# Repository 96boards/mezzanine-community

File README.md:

# 96boards Community Mezzanine Initiative

## About this Project

This is a community led, organized and maintained initiative. This repository is for designing mezzanine addon boards based on the 96Boards family of [96boards specifications](https://www.96boards.org/specifications/).

## Contributing and Reporting Issues

Community contributions are always Welcome! Before contributing to a project, first get the approval from maintainer by raising a GitHub issue using the following guidelines.

Take a look at our [CONTRIBUTE.md](CONTRIBUTE.md) page for more info.

## Roadmap and Wishlist

- Quantized community 96Boards Mezzanine input
- More boards!

## Meetings and notes

An informal steering committee of community members will allocate resources to a variety or projects, all with a grand scope of meeting the needs of the greater 96Boards community.

-  Bi Weekly voice/video conference meetings are open to the public on the 96Boards Discord Server. Join every Every 2 weeks on Monday at 16:00 UTC to take part in the discussion.
   - https://discord.gg/TC3pv8XcN8
- [View notes](https://github.com/96boards/mezzanine-community/issues?q=is%3Aissue+is%3Aopen+label%3AMeeting) from previous meetings

## Acknowledgement

- T.Krug @sad_electronics - Lead Maintainer
- Michael Welling, mwelling@ieee.org - Maintainer
- Robert Wolff, robert.wolff@linaro.org - Community
- Rafael Christ, rafaelchrist@gmail.com - Altium / Eagle Reviewer
- Gustavo Retuci Pinheiro, gustavo_r_p@hotmail.com - Altium / Eagle Reviewer
- Sahaj Sarup, sahajsarup@gmail.com - Reviewer
- Grant Likely, grant.likely@secretlab.ca - KiCad contributor
- Sophie Haynes - KiCad contributor

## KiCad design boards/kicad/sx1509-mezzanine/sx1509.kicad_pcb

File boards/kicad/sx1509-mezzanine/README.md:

# 96boards Mezzanine Project Template

This template provides you with all the base files required for 
a 96Boards mezzanine pcb project.

#### Template Folder Contents:

- COPYING (license)
- meta
- 96boards.pretty (folder containing footprints) °
- mezza-cache.lib ° (system file, ignore)
- mezza.pro °
- mezza.sch °
- mezza.kicad_pcb °
- fp-lib-table °

*Files marked with ° are the KiCad project files*

## To-Do's

Coming soon...

## What is this template for?

This is a template for anyone who wants to develop a Consumer Edition 96Boards
Mezzanine board - [List of Consumer Edition Boards](https://www.96boards.org/products/ce/)

This schematic only contains the necessary connectors needed
for a mezzanine board. By default it is set up for SMD connectors, but
can easily be changed to through-hole.

The <em>PCB</em> includes the connectors and mounting holes. The holes
and connectors have been positioned so that the boards are aligned when
mounted. The <em>edge cuts</em> also aligns with the base board. All the
mezzanine board low-speed expansion connector <em>IO</em> is connected
to the header pins. High-speed expansion IO has not yet been added.

## How to use this project

This project has been formatted to work with KiCad's "New Project from
Template" tool. You should clone this project into your KiCad templates
directory. For example, on OSX the system template directory is
<em>/Library/Application Support/kicad/template/</em>. A Linux user's
template directory is <em>$HOME/kicad/template/</em>

Once cloned, you can use the new template by navigating to
File > New Project > New Project From Template. After selecting your
save location, click on <em>System Templates</em> or <em>User
Templates</em> (depending on which file path you previously selected to
clone the project to). Upon validation of the file path, the 96Boards
mezzanine template should appear under the 96Boards logo. Select the
template and you'll be good to go.

## Changing to Through Hole Connector

By default, this project loads with the connectors set up as SMD. If you
would prefer to use a through hole instead, follow the instructions on
the schematic to delete a connector and change the footprint on the
other. To change the footprint, right click and select <em>Edit
Component</em>. In the dialog box, click on the footprint section, then
on the right there should now be a button called <em>Assign
Footprint</em>. Click the button, and choose the different footprint
file. Create a new netlist file, open up the PCB editor, and <em>Load
Netlist</em>, ensuring that <em>Exchange Footprint</em> is set to
CHANGE, and <em>Extra Footprints</em> is set to DELETE. Click <em>Read
Current Netlist</em> to load the new connector. Now you should have only
one connector on the board, and when you view in 3D view, there will be
a through hole connector.

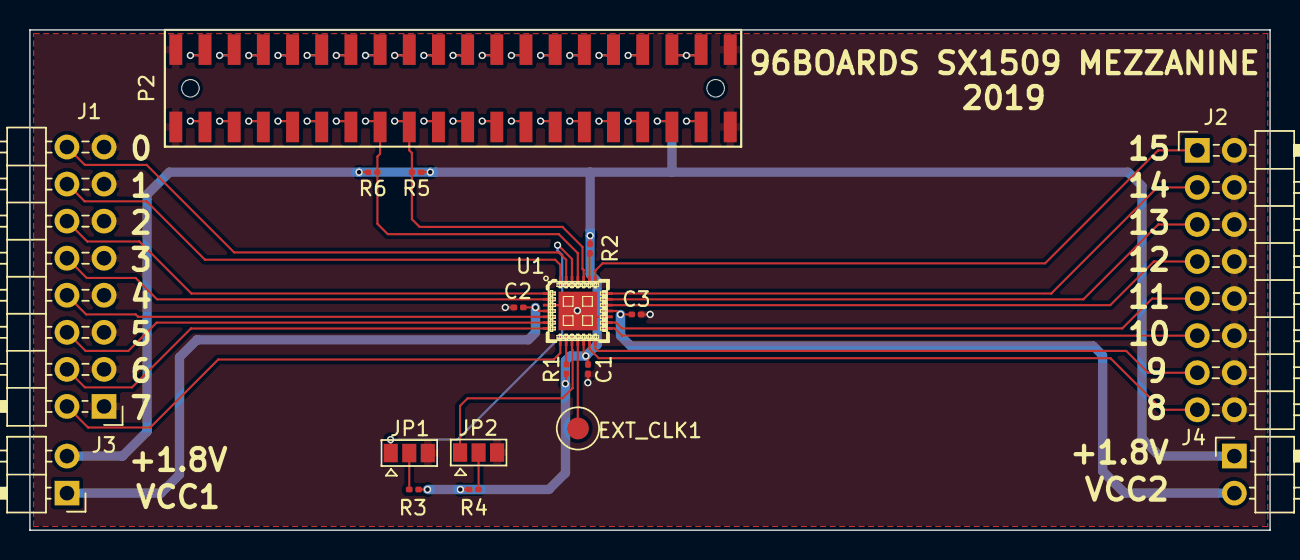
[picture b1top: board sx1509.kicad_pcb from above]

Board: 2 copper layers, 85.0 x 34.3 mm, 19 parts (1 on the bottom side), 61 nets.

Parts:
C1, C2, C3: 0.1uF; C_0201_0603Metric
EXT_CLK1: TestPoint; TestPoint_Pad_D2.5mm
J1, J2: Conn_02x08_Odd_Even; PinHeader_2x08_P2.54mm_Horizontal
J3, J4: Conn_01x02_Male; PinHeader_1x02_P2.54mm_Horizontal
JP1, JP2: Jumper_NC_Dual; SolderJumper_01x03
P1: CONN_02X20; Pin_Header_SMD_2x20_Pitch2mm
P2: CONN_02X20; Socket_Strip_SMD_2x20_Pitch2mm
R1, R2, R3, R4, R5, R6: 10K; R_0201_0603Metric
U1: SX1509; QFN-28

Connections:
+1V8: C1.1, J3.2, J4.1, P1.35, P2.35, R1.2, R2.2, R3.2, R4.1, R5.1, R6.1, U1.12
+5V: P1.37, P2.37
ADDR0: JP1.1, U1.26
ADDR1: JP2.1, U1.10
GND: C1.2, C2.2, C3.2, J1.1, J1.3, J1.5, J1.7, J1.9, J1.11, J1.13, J1.15, J2.2, J2.4, J2.6, J2.8, J2.10, J2.12, J2.14, J2.16, JP1.3, JP2.3, P1.1, P1.2, P1.39, P1.40, P2.1, P2.2, P2.39, P2.40, U1.3, U1.17, U1.29
GPIO_A: P1.23, P2.23
GPIO_B: P1.24, P2.24
GPIO_C: P1.25, P2.25
GPIO_D: P1.26, P2.26
GPIO_E: P1.27, P2.27
GPIO_F: P1.28, P2.28
GPIO_G: P1.29, P2.29
GPIO_H: P1.30, P2.30
GPIO_I: P1.31, P2.31
GPIO_J: P1.32, P2.32
GPIO_K: P1.33, P2.33
GPIO_L: P1.34, P2.34
I2C0_SCL: P1.15, P2.15, R6.2, U1.25
I2C0_SDA: P1.17, P2.17, R5.2, U1.24
I2C1_SCL: P1.19, P2.19
I2C1_SDA: P1.21, P2.21
IO_0: J1.16, U1.27
IO_1: J1.14, U1.28
IO_2: J1.12, U1.1
IO_3: J1.10, U1.2
IO_4: J1.8, U1.5
IO_5: J1.6, U1.6
IO_6: J1.4, U1.7
IO_7: J1.2, U1.8
IO_8: J2.15, U1.13
IO_9: J2.13, U1.14
IO_10: J2.11, U1.15
IO_11: J2.9, U1.16
IO_12: J2.7, U1.19
IO_13: J2.5, U1.20
IO_14: J2.3, U1.21
IO_15: J2.1, U1.22
unnamed: EXT_CLK1.1, U1.11
unnamed: JP1.2, R3.1
unnamed: JP2.2, R4.2
unnamed: R1.1, U1.9
unnamed: R2.1, U1.23
PCM_CLK: P1.18, P2.18
PCM_DI: P1.22, P2.22
PCM_DO: P1.20, P2.20
PCM_FS: P1.16, P2.16
PWR_BTN_N: P1.4, P2.4
RST_BTN_N: P1.6, P2.6
SPIO_CS: P1.12, P2.12
SPIO_DIN: P1.10, P2.10
SPIO_DOUT: P1.14, P2.14
SPIO_SCL: P1.8, P2.8
SYS_DCIN: P1.36, P1.38, P2.36, P2.38
UART0_CTS: P1.3, P2.3
UART0_RTS: P1.9, P2.9
UART0_RX: P1.7, P2.7
UART0_TX: P1.5, P2.5
UART1_RX: P1.13, P2.13
UART1_TX: P1.11, P2.11
VCC1: C2.1, J3.1, U1.4
VCC2: C3.1, J4.2, U1.18

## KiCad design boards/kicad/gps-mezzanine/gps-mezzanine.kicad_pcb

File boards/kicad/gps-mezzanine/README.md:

# 96boards GPS Mezzanine

This project contains the design files for a GPS mezzanine for the 96boards CE specification.

Copyright (c) 2017-2018, Michael Welling

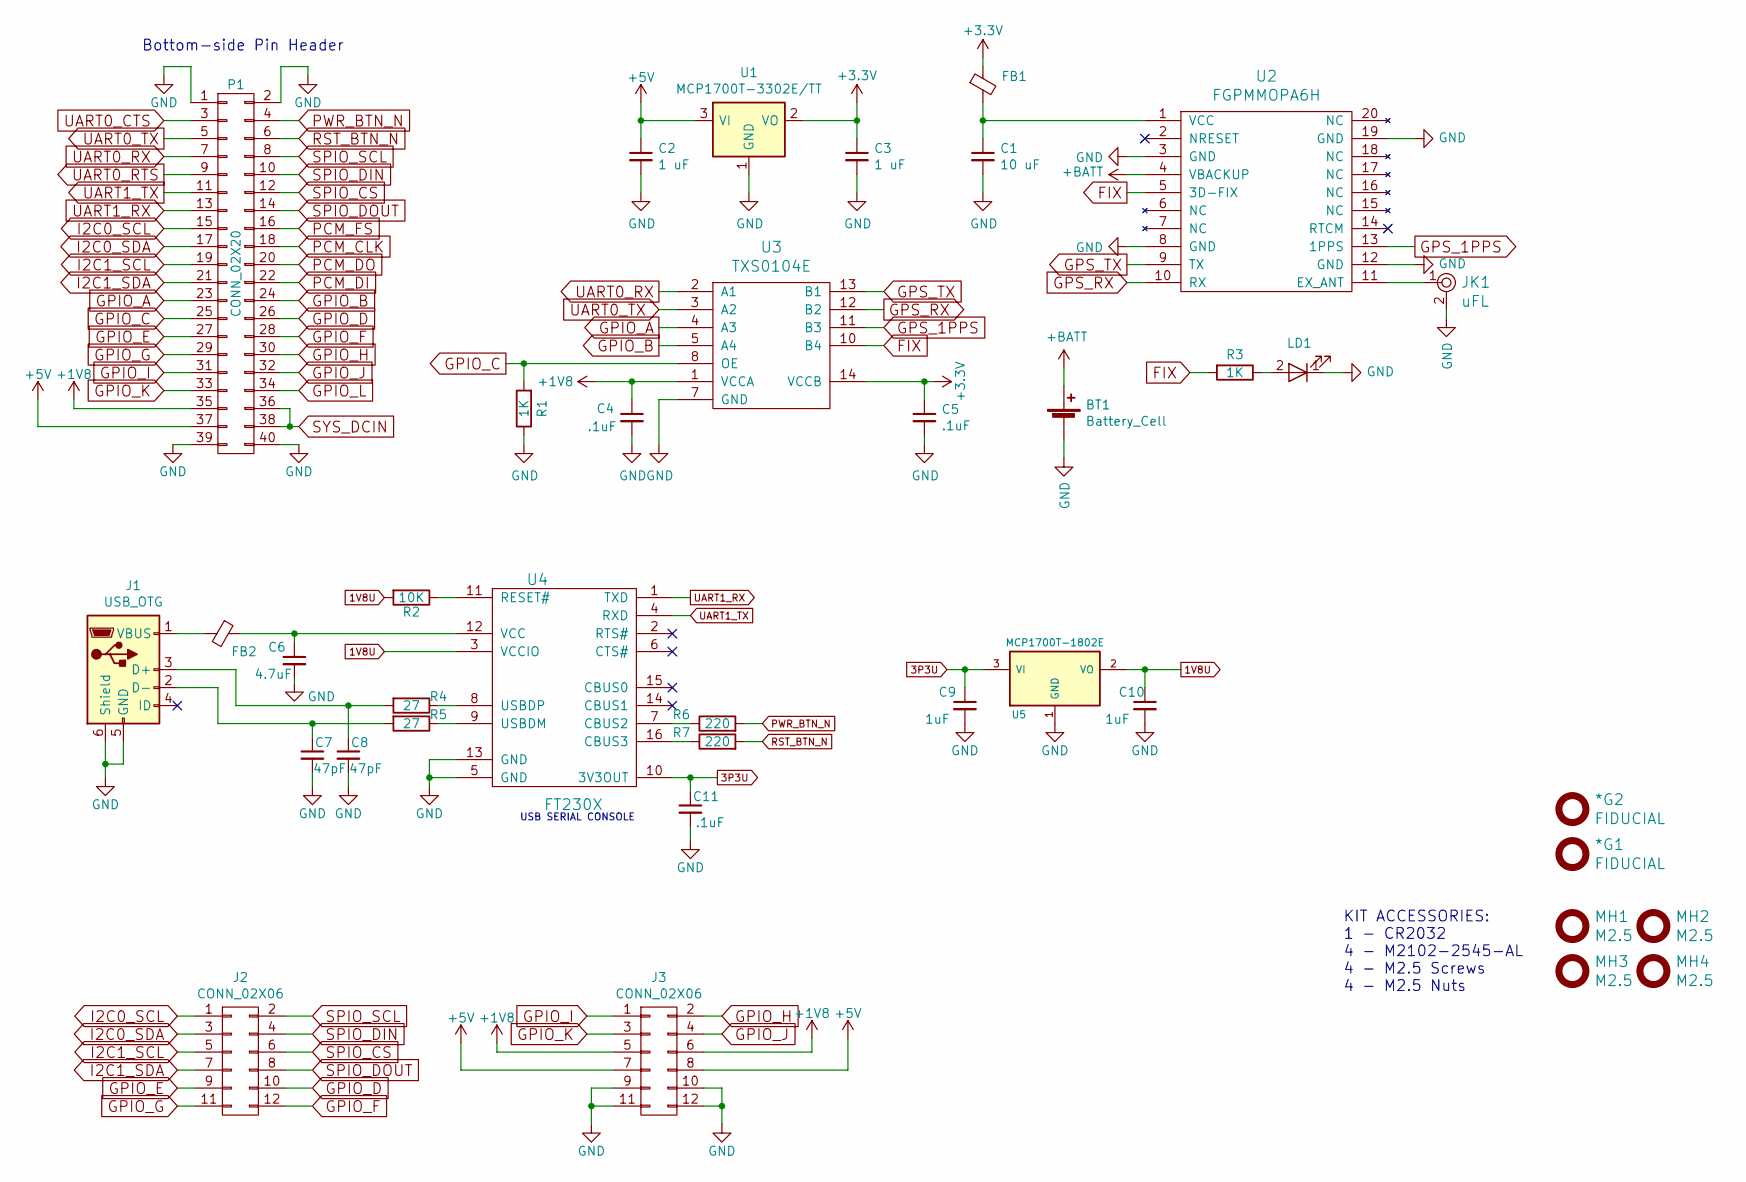
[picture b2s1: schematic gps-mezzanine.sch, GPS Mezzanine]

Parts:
*G1, *G2: FIDUCIAL; Fiducial_1mm_Dia_2.00mm_Outer_CopperTop
BT1: Battery_Cell; BAT-HLD-001; Mfg Part Number BAT-HLD-001-TR
C1: 10 uF; C_0603
C2, C3: 1 uF; C_0603
C4, C5, C11: .1uF; C_0603
C6: 4.7uF; C_0603
C7, C8: 47pF; C_0603
C9, C10: 1uF; C_0603
FB1, FB2: ILBB0805ER102V; R_0805_HandSoldering; Mfg Part Number ILBB0805ER102V
J1: USB_OTG; 10118192-0001LF(MICRO-USB-B-AMPHENOL-FCI); Mfg Part Number 10118192-0001LF
J2, J3: CONN_02X06; Pin_Header_Straight_2x06
JK1: uFL; U.FL-R-SMT-1; Mfg Part Number U.FL-R-SMT-1
LD1: LED; LED-0603
MH1, MH2, MH3, MH4: M2.5; MountingHole_2-5mm
P1: CONN_02X20; Pin_Header_SMD_2x20_Pitch2mm; Mfg Part Number 57202-G52-20LF
R1, R3: 1K; R_0603
R2: 10K; R_0603
R4, R5: 27; R_0603
R6, R7: 220; R_0603
U1: MCP1700T-3302E/TT; SOT-23; Mfg Part Number MCP1700T-3302E/TT
U2: FGPMMOPA6H; Mfg Part Number FGPMMOPA6H
U3: TXS0104E; TSSOP-14_4.3x5.1mm_Pitch0.65mm; Mfg Part Number TXS0104EPWR
U4: FT230X; SSOP-16_3.9x4.9mm_Pitch0.635mm; Mfg Part Number FT230XS-R
U5: MCP1700T-1802E; SOT-23; Mfg Part Number MCP1700T-1802E/TT

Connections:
1V8U: C10.1, R2.2, U4.3 (VCCIO), U5.2 (VO)
3P3U: C9.1, C11.1, U4.10 (3V3OUT), U5.3 (VI)
+1V8: C4.1, J3.5, J3.6, P1.35, U3.1 (VCCA)
+3V3: C3.1, C5.1, FB1.1, U1.2 (VO), U3.14 (VCCB)
+5V: C2.1, J3.7, J3.8, P1.37, U1.3 (VI)
+BATT: BT1.1 (+), U2.4 (VBACKUP)
FIX: R3.2, U2.5 (3D-FIX), U3.10 (B4)
GND: BT1.2 (-), C1.2, C2.2, C3.2, C4.2, C5.2, C6.2, C7.2, C8.2, C9.2, C10.2, C11.2, J1.5 (GND), J1.6 (Shield), J3.9, J3.10, J3.11, J3.12, JK1.2, LD1.1 (K), P1.1, P1.2, P1.39, P1.40, R1.1, U1.1 (GND), U2.3 (GND), U2.8 (GND), U2.12 (GND), U2.19 (GND), U3.7 (GND), U4.5 (GND), U4.13 (GND), U5.1 (GND)
GPIO_A: P1.23, U3.4 (A3)
GPIO_B: P1.24, U3.5 (A4)
GPIO_C: P1.25, R1.2, U3.8 (OE)
GPIO_D: J2.10, P1.26
GPIO_E: J2.9, P1.27
GPIO_F: J2.12, P1.28
GPIO_G: J2.11, P1.29
GPIO_H: J3.2, P1.30
GPIO_I: J3.1, P1.31
GPIO_J: J3.4, P1.32
GPIO_K: J3.3, P1.33
GPIO_L: P1.34
GPS_1PPS: U2.13 (1PPS), U3.11 (B3)
GPS_RX: U2.10 (RX), U3.12 (B2)
GPS_TX: U2.9 (TX), U3.13 (B1)
I2C0_SCL: J2.1, P1.15
I2C0_SDA: J2.3, P1.17
I2C1_SCL: J2.5, P1.19
I2C1_SDA: J2.7, P1.21
unnamed: C1.1, FB1.2, U2.1 (VCC)
unnamed: C6.1, FB2.1, U4.12 (VCC)
unnamed: C7.1, J1.2 (D-), R5.2
unnamed: C8.1, J1.3 (D+), R4.2
unnamed: FB2.2, J1.1 (VBUS)
unnamed: JK1.1, U2.11 (EX_ANT)
unnamed: LD1.2 (A), R3.1
unnamed: R2.1, U4.11 (RESET#)
unnamed: R4.1, U4.8 (USBDP)
unnamed: R5.1, U4.9 (USBDM)
unnamed: R6.1, U4.7 (CBUS2)
unnamed: R7.1, U4.16 (CBUS3)
PCM_CLK: P1.18
PCM_DI: P1.22
PCM_DO: P1.20
PCM_FS: P1.16
PWR_BTN_N: P1.4, R6.2
RST_BTN_N: P1.6, R7.2
SPIO_CS: J2.6, P1.12
SPIO_DIN: J2.4, P1.10
SPIO_DOUT: J2.8, P1.14
SPIO_SCL: J2.2, P1.8
SYS_DCIN: P1.36, P1.38
UART0_CTS: P1.3
UART0_RTS: P1.9
UART0_RX: P1.7, U3.2 (A1)
UART0_TX: P1.5, U3.3 (A2)
UART1_RX: P1.13, U4.1 (TXD)
UART1_TX: P1.11, U4.4 (RXD)

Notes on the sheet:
Bottom-side Pin Header
KIT ACCESSORIES: 1 - CR2032 4 - M2102-2545-AL 4 - M2.5 Screws 4 - M2.5 Nuts
USB SERIAL CONSOLE

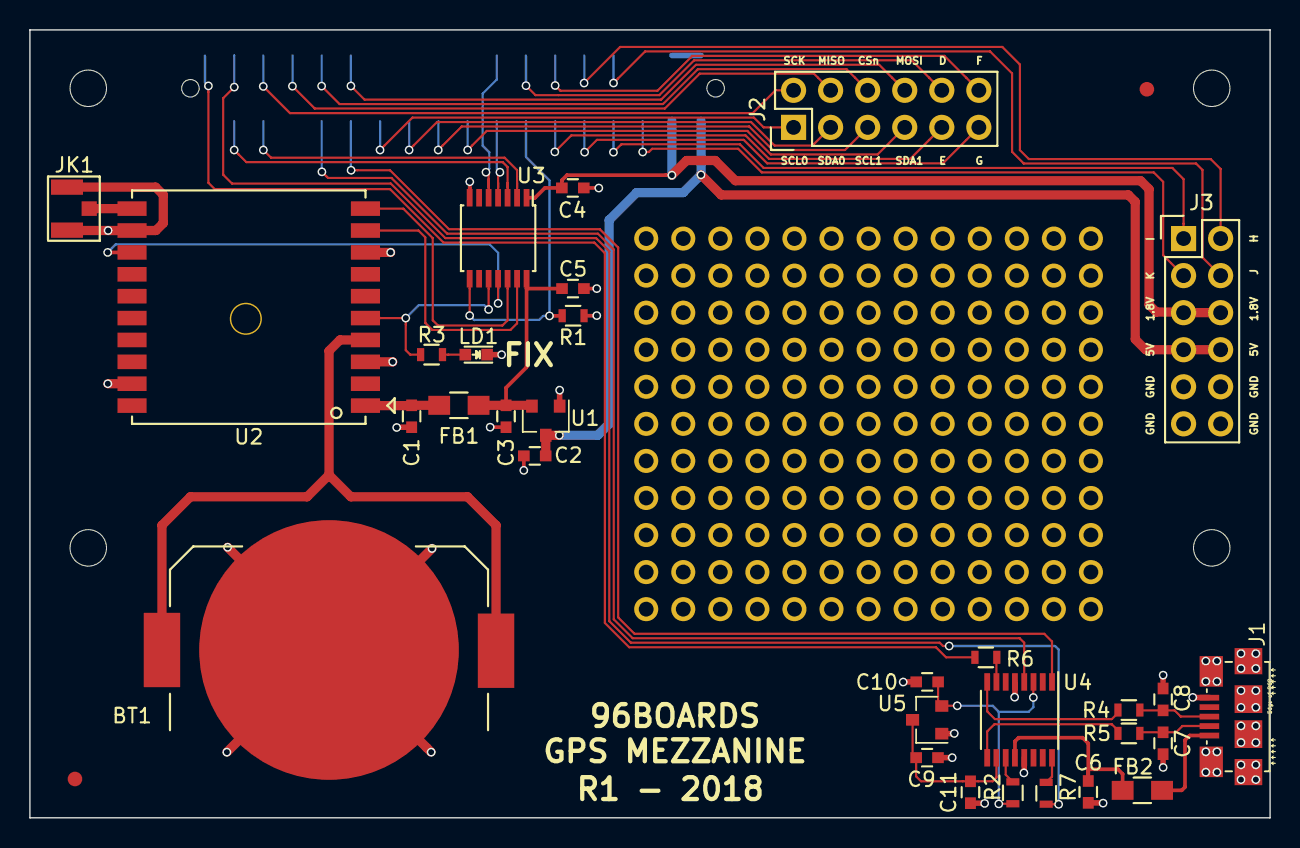
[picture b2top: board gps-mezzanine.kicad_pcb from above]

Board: 2 copper layers, 85.0 x 54.0 mm, 38 parts (1 on the bottom side), 49 nets.

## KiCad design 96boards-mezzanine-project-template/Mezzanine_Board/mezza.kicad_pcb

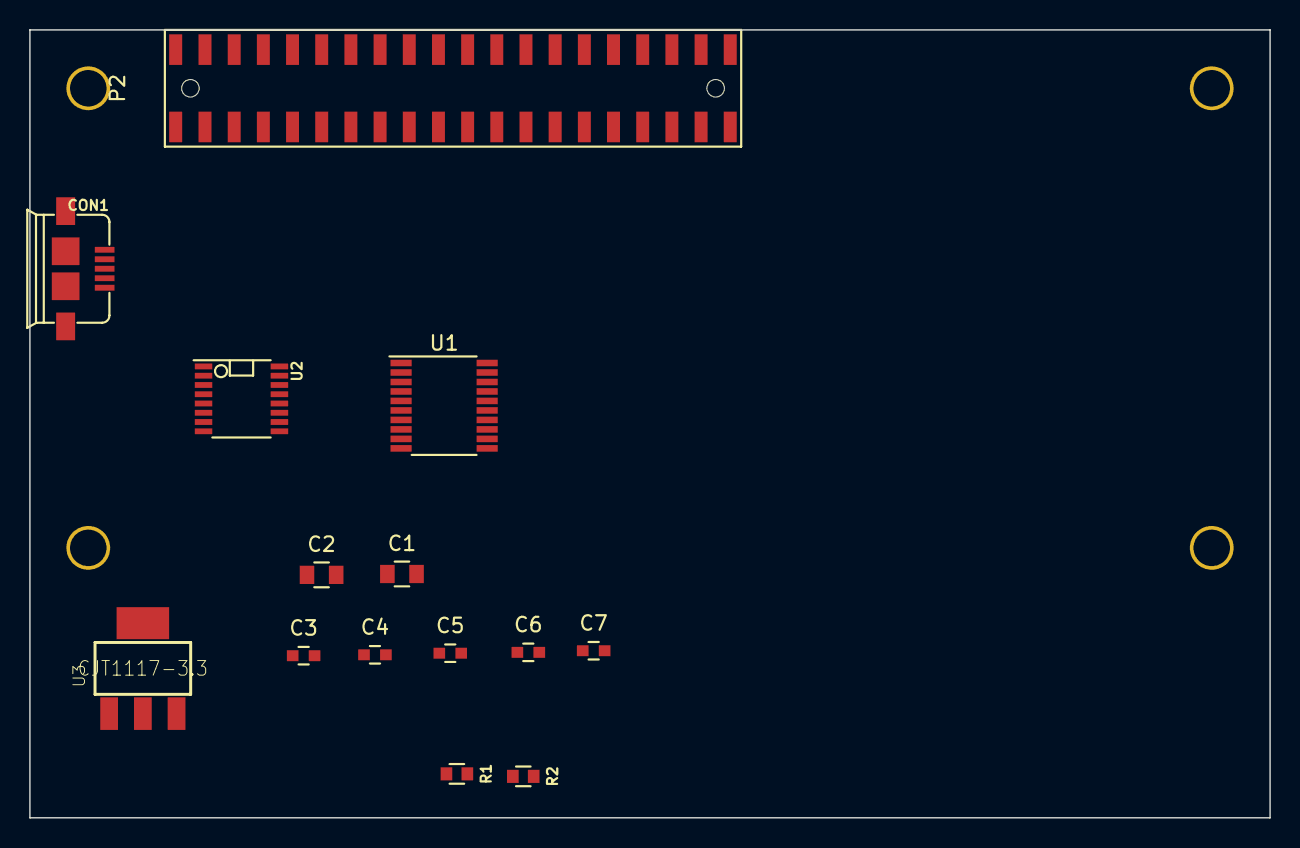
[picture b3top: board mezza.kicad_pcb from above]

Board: 2 copper layers, 85.0 x 54.0 mm, 15 parts (1 on the bottom side), 23 nets, no tracks yet.

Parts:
C1, C2: 1uF; C_0805
C3, C7: 100nF; C_0603
C4, C5: 39pF; C_0603
C6: 1uF; C_0603
CON1: USB-MINI-B; USB_MICRO_B_ST-USB-001E
P1: CONN_02X20; Socket_Strip_SMD_2x20_Pitch2mm
P2: CONN_02X20; Pin_Header_SMD_2x20_Pitch2mm
R1, R2: 22R; R_0603_Seeed
U1: TXS0108E; TSSOP-20_4.4x6.5mm_Pitch0.65mm
U2: FT230XS; SSOP-16_3.9x4.9mm_Pitch0.635mm_Seeed
U3: CJT1117-3.3; SOT223

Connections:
+1V8: C2.1, P1.35, P2.35, U2.3, U3.2
+3V3: C1.1, U1.2, U3.3
+3V3_FTDI: C3.1, U2.10, U2.11
+5V: P1.37, P2.37
GND: C1.2, C2.2, C3.2, C4.2, C5.2, C6.2, C7.2, CON1.5, CON1.6, CON1.7, CON1.8, CON1.9, P1.1, P1.2, P1.39, P1.40, P2.1, P2.2, P2.39, P2.40, U1.11, U2.5, U2.13, U3.1
GPIO-A: P1.23, P2.23, U1.6
GPIO-B: P1.24, P2.24, U1.7
I2C0_SCL: P1.15, P2.15, U1.1
I2C0_SDA: P1.17, P2.17, U1.5
I2C1_SCL: P1.19, P2.19, U1.3
I2C1_SDA: P1.21, P2.21, U1.4
unnamed: C4.1, CON1.2, R1.2
unnamed: C5.1, CON1.3, R2.2
unnamed: R1.1, U2.9
unnamed: R2.1, U2.8
PWR_BTN_N: P1.4, P2.4, U2.7
RST_BTN_N: P1.6, P2.6, U2.16
SYS_DCIN: P1.36, P1.38, P2.36, P2.38
UART_CTS: P1.3, P2.3, U2.2
UART_RTS: P1.9, P2.9, U2.6
UART_RX: P1.7, P2.7, U2.1
UART_TX: P1.5, P2.5, U2.4
VBUS: C6.1, C7.1, CON1.1, U2.12

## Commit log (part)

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2015-11-23 Populate the Git Repository
    Add 'Specification' to the repo.
    Includes a copy of 96board specification.
    This serves as a holding place for any specification files the user may have.
    Add 'Production_Files' to the repo.
    When the user has production file (eg gerber), they should store them in this
    folder.
2015-11-26 Add License
    This commit adds the BSD license file to the project.
2015-11-27 Flip USB Connector, Rename GPIO Signals, Remove Level Shifter
    The USB connector has been flipped so that the data signals are cleaner.
    Regulator has been changed from CJT1117-3.3 (which regulates to 3.3V)
    to XC6206 (which regulates to 1.8V).
    GPIO-A & GPIO-B have been changed to "GPIO_A" & "GPIO_B" to keep consistent
    with rest of signal names.
    Level shifter has been removed temporarily.
2015-11-28 Add LED Indication for RX/TX
    An LED wired to CBUS0 & CBUS1 has been added to show RX/TX activity.
    Connected to +5V and both lines have 220R.
2015-11-28 Add PWR LED, Remove 2nd Expansion Conn. Footprint
    LED's for each power rail have been added (+5V, +3V3, +1V8) to show when
    each is live.
    The footprint for the second expansion connector has been removed so that it
    is now a standard through-hole port.
2015-12-03 Move USB Connector
    USB connector has been moved to the same position as the 96Boards Sensors
    board.
    Components that are not connectors have been removed from the schematic.
2015-12-09 Add 3v3_F Component & Change Power Signals According
    A new power component has been added to the mezza library (3v3_F). This is to
    replace '3v3_FTDI' and serve as an individual power source for specific
    components.
2015-12-28 Add PWR LED for 1V8_F
    Added a LED for the 1V8_F power rail to indicate it's powered on.
2015-12-30 Add Missing lib File (Debug)
    When trying to append the schematic, the project requires this library to load
    all components.
2016-01-08 Resize Meta Icon & Correct Copyright Rights
    Image has been scaled so it looks pretty in template selector.
    Copyright has been corrected in meta info.html
2016-01-08 Add a .gitignore file
    Make it easier to see if there are repo changes by ignoring the
    unimportant files.
2016-01-08 Change Connector Footprints
    The former footprints were incorrect as they caused the sockets to move on the
    pcb. These have been corrected.
2016-01-08 Remove Unneeded .lib Files
    The .lib files have been removed as they are not used in the project at this
    time. I have re-added the mezza-cache.lib as it is the backup for the project.
2016-01-11 Finalize readme.md & info.html Content
    Content has been updated to match the current status of the project.
2016-01-11 Remove Test Plan
    Test plan is not a part of the template therefore is being removed.
2016-01-14 Update (c) & 'How to Use This Project'
    The copyright in both files have been updated to 2016.
    Instructions in the readme.md on how to use this project have been corrected
    so that the file paths are included, and no longer mention the test plan.
2016-01-14 Fix Pad Placement For Mounting Holes
    With all the changes made over time, two of the mounting holes
    has shifted slightly out of place. This has been rectifed.
2016-01-14 Flip P1/2 Board Side Placement
    Looking at the 3D model, it appears that P1 (which has the socket footprint)
    was attatched to the rear of the board, and P2 (which has pins) was located on
    the top of the board. They have been switched round manually and realigned to
    their former positions.
2016-01-14 Add DIP Footprint & Model
    A new footprint has been added for users who want to use a through hole
    connector instead of the surface mounted ones.
    The 3D model file has been stored in the 96boards.pretty folder.
2016-01-22 Update project files
2016-01-29 Revert "Update P1/2 Footprints" to bring back SMD footprints
    This reverts commit 6c9482137aee05ae7fa74c414fdf955d67f2f11d.
    We want to provide the option of either SMD or through-hole connector,
    instead of either/or. Revert the removal of the SMD footprints so the
    user can choose which one they want to use.
2016-01-29 Default to SMD footprints on layout
    Default to using SMD connectors on the layout. The user can choose to
    switch to through-hole connectors if they so desire by deleting one of
    the schematic objects and switching the footprint.
2016-01-29 Add dimension markings to layout and correct hole positions
    Add dimension markings to the template so that users can see exactly how
    things are placed and compare them with the 96Boards spec. At the same
    time, fix the position of 2 of the mounting holes and lock all the
    footprints so they don't get accidentally changed.
2016-01-29 Update the readme file
    There were a few inaccuracies in the readme file. Bring it up to date
    and tidy up some of the language.
2017-07-18 Added initial layout with some information
2017-07-21 Added boards and meetings sections/folders
    boards archive will contain all boards we are currently
    working on. meetings folder will allow us to log notes from
    previous meetings to make community entry a little easier.
2017-07-21 Added initial content for boards README.md
    This content structure is up for discussion
2017-07-24 Update meeting link in README
2017-07-26 Added board-template folder
    This folder will contain all the necessary materials needed
    to add a new board to the repository. Once it has been accepted
    by the committee through decided process.
2017-08-06 Move files into template directory
    In preparation for merging with community mezzanine project.
2017-08-07 Remove template folder in board
    The template is now in a top level template folder.
2017-08-07 Update toplevel README
2017-08-07 Step 1/2 renaming readme.md to README.md
2017-08-07 Add 07-31 meeting to past sessions list
2017-08-07 Change the case of the readme.md for consistency
2017-08-07 Initial commit of Proto Mezzanine
    Converted from Upverter design by Barry Byford.
2017-08-07 Tweak the README for grammar
2017-08-07 Add an image to the README for grins
2017-08-07 Added template folders and readme's
2017-08-07 Fix README text
2017-08-07 Add IoT_6LoWPAN_gateway_v01 mezzanine
2017-08-08 Added meeting notes from 08-07-17
2017-08-08 Add corrections to file names
2017-08-08 Altium template creation
2017-08-09 Images & keepout
2017-08-09 README
2017-08-10 IO-testing
2017-08-11 Add high speed connector to kicad template
    Schematic connector added with net names.
    3D model included for PCB footprint.
2017-08-14 Changes to Boards landing page README.md
2017-08-14 Added relative links to various boards
2017-08-14 Fix relative links
    The links pointed to the wrong subdirectory.
2017-08-14 Add Gerber plots for preliminary testing release
2017-08-14 pinout fix
2017-08-15 Add 96Boards Mezzanine EagleCAD template
2017-08-15 Small change in README.md
2017-08-15 Added readme.md for high level board files
2017-08-15 Fixed relative link for eagle design files readme.md
2017-08-15 Fixed relative link to design files
2017-08-15 Added relative link to IO testing mezzanine
2017-08-15 Add line break for prettier README rendering
2017-08-17 Add placeholder for new design
    Design will be added upon approval.
2017-08-28 Rename 08-21-17.md to 08-28-17.md
2017-08-28 Fix meeting links
    Links were pointing to a previous meeting.
2017-09-01 IO testing Stackable
2017-09-04 Initial commit of the GPS mezzanine
    TODO: Add battery and external antenna connector.
2017-09-11 Rename 09-04-17.md to 09-11-17.md
2017-10-13 Include Sophie and Grant in the contributors list
    Sophie Haynes and Grant Likely created the KiCad template. They should
    be listed in the acknowledgements.
2017-10-13 KiCad template: Add footprints for CE form factors
    Add footprints for each of the 96Boards CE form factors; standard,
    extended-A and extended-B. The footprint contains the correct size and
    position of the mounting holes, the position of each of the expansion
    connectors, and the dimensions of the keepout areas. Adding one of these
    footprints to a board design will make it much easier to make sure
    everything is lined up correctly.
2017-11-06 Fixes issues found on first revision
    Moves USB connector to align with the one below it.
    Adds a Nch MOSFET to drive the LEDs from the 1.8V GPIO.
    Changes the connection to the switches.
    Updates silkscreen slightly to be more tidy.
2017-11-06 Add MOSFET datasheet
    Add datasheet for the Nch MOSFET used for LEDs.
2017-11-09 Update README link for update directory names
    The IO mezzanine directories changes with the latest commits.
2017-11-20 docs: Improve CONTRIBUTE.md and README.md
    - Add detailed contribution guidelines
    - Cange meeting link from legacy repo folder to issues with "Meeting" lable
    - Other misc. changes
2017-12-01 Add UART header and schematic PDF
2018-04-02 Initial Readme and schematic PDF
2018-05-05 Add ferrite bead to GPS power supply
2018-05-05 Increase hole for internal antenna on GPS module
2018-05-05 Increase board size to full form factor
    To make room for prototyping area and possible USB UART.
2018-05-08 Add a picture to the README
2018-05-08 Add image of schematic in PNG format
2018-05-19 Updates for maufacturing
    Adds fiducials for manufacturing.
    Switches to SMT USB connector.
    Fixes pattern for the level translator.
    Adds QWERTY logo to the bottom of the board.
2018-06-21 Fixed time of meeting
    Meeting was listed as 17:00 UTC when it should be 16:00 UTC
2018-07-07 Initial schematics for i2s-mezzanine sound card
    These schematics are a subset of a much more complex project I have
    been working on, and are probably a good head start on an i2s
    mezzanine.
    The PCM DI and DO of the 96boards LS port are connected to GPIO0 and
    GPIO1 of the pcm1865 respectively. GPIO0 is to be configured as
    DOUT2, GPIO1 is to be configured as DIN. This is done by setting
2018-07-25 Option to isolate GPIO-K and keep the regulator on always.
    This would be necessary if a board stacked above or below this
    board also requires GPIO-K, otherwise, we can add a regulator
    driver to the kernel and have the pcm186x and pcm512x drivers
    manage regulator power state.
2018-07-27 I2S Mezzanine: Fix overshot wire at R403 schematic
    Probably the whole wire moved when the intention was to move the end.
2018-07-27 I2S Mezzanine: Remove superfluous via at U301
2018-07-27 I2S Mezzanine: Move traces further from edge of board
2018-07-27 I2S Mezzanine: Change to surface mount LS connectors, license
2018-07-27 I2S Mezzanine: Add gerber files
2018-07-27 I2S Mezzanine: Add README
2018-07-28 I2S Mezzanine: Move CONN501 closer to edge of board.
    Same distance as all other plugs.
2018-09-17 I2S Mezzanine: Change crystal load capacitors to 22 pF
2018-09-17 I2S Mezzanine: Update gerbers
2018-10-03 Update README
    The text said KiCAD but this is the gEDA directory.
2018-10-15 add staging folder
2018-11-18 Mechanical guide
2019-02-21 Proto mezzanine updated to v1.4
    Changes
    - Labled i2c -> i2c0
    - Removed pads from lower third to stop interference with ports on base board
    - Reduced size of the board on the Y-axis
2019-05-23 Clean up design
    The placement, routing, and silkscreen were updated to look nicer.
2019-05-23 Update SX1509 mezzanine silkscreen
    Adds GPIO numbering to the silkscreen.
2020-11-02 Updated README with Current Info
2020-11-05 Update COPYING
2021-04-27 Add A13 as maintainer
